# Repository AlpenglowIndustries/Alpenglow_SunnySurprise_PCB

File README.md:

# Alpenglow_SunnySurprise_PCB
Kicad files for learn to solder PCB

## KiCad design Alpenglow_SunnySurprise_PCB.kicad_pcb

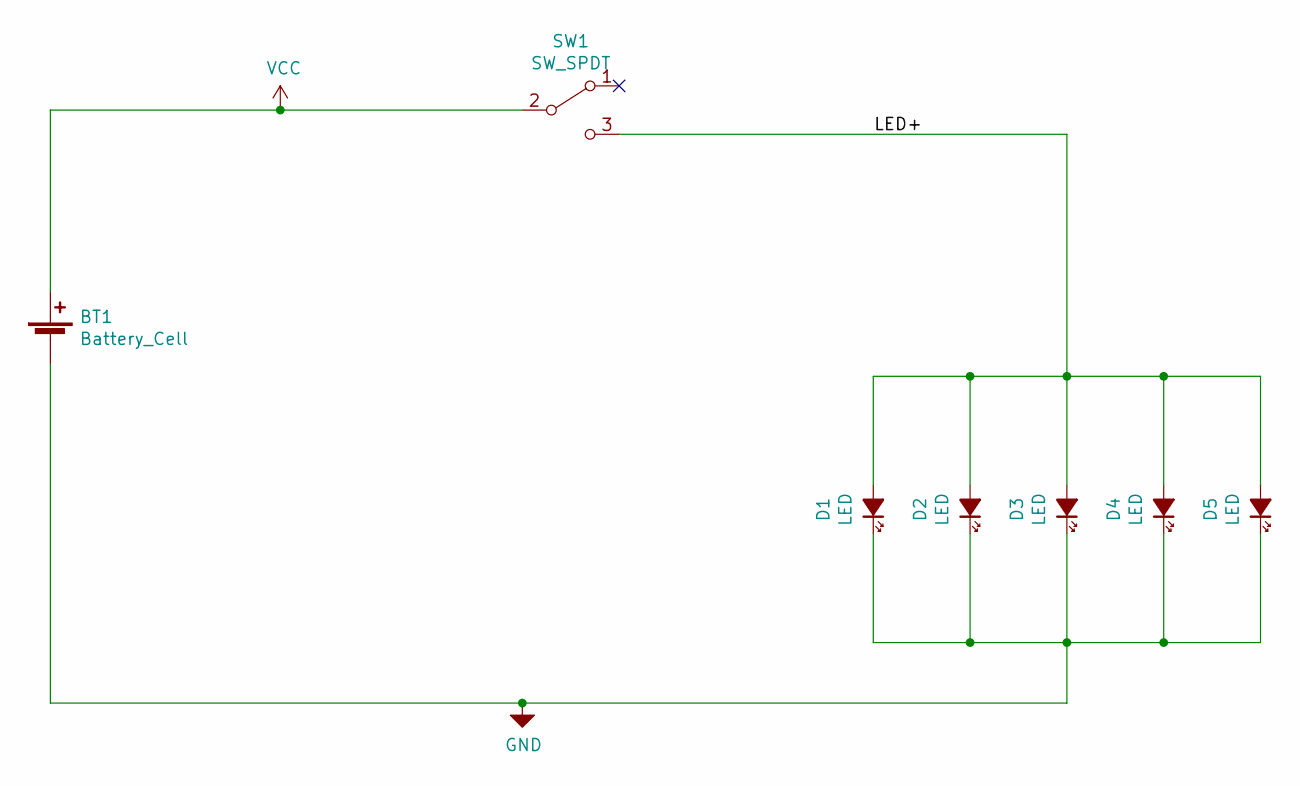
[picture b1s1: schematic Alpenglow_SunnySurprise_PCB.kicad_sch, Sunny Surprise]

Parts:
BT1: Battery_Cell; BatteryHolder_MPD_BK888_2032_THRU
D1, D2, D3, D4, D5: LED; LED_D5.0mm_Horizontal_Sun
SW1: SW_SPDT; Alpenglow_SW_SPDT_3pin_RTA

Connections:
/LED+: D1.2 (A), D2.2 (A), D3.2 (A), D4.2 (A), D5.2 (A), SW1.3 (C)
GND: BT1.2 (-), D1.1 (K), D2.1 (K), D3.1 (K), D4.1 (K), D5.1 (K)
VCC: BT1.1 (+), SW1.2 (B)

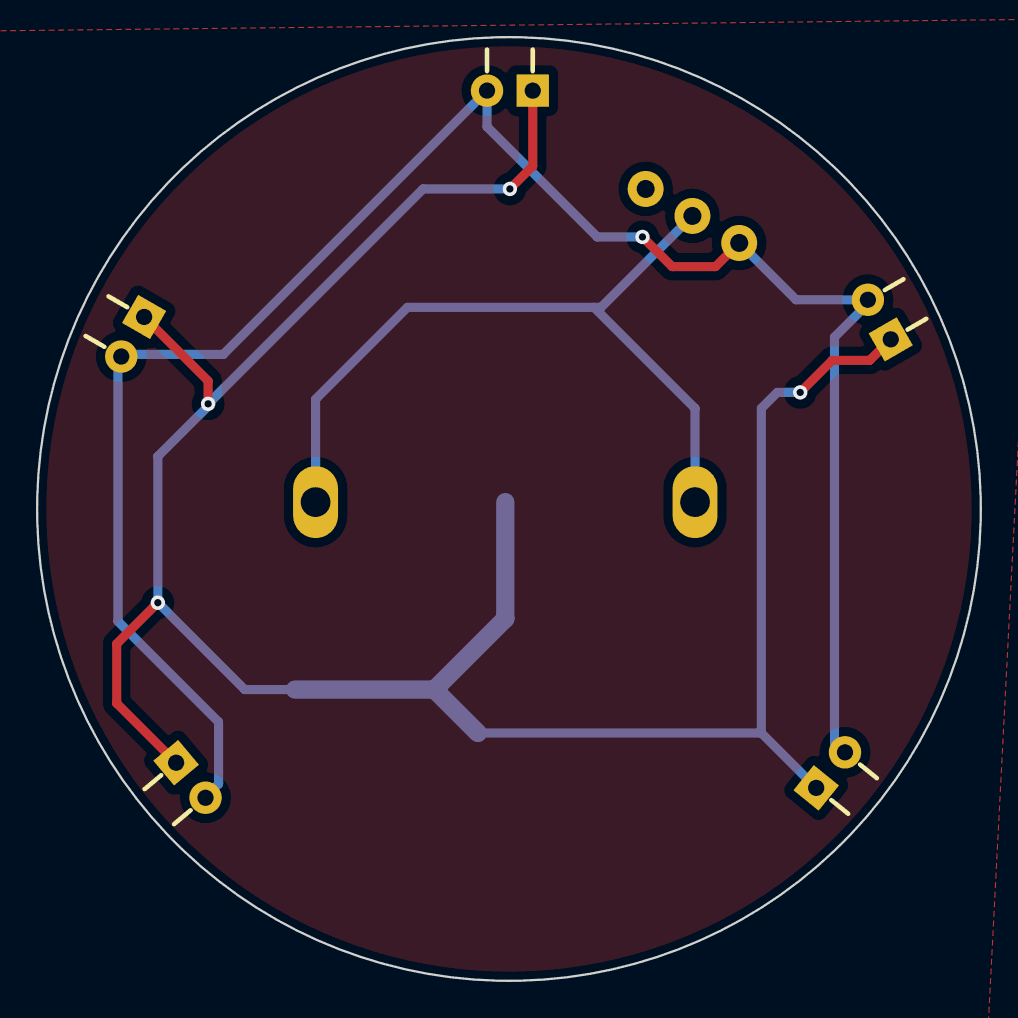
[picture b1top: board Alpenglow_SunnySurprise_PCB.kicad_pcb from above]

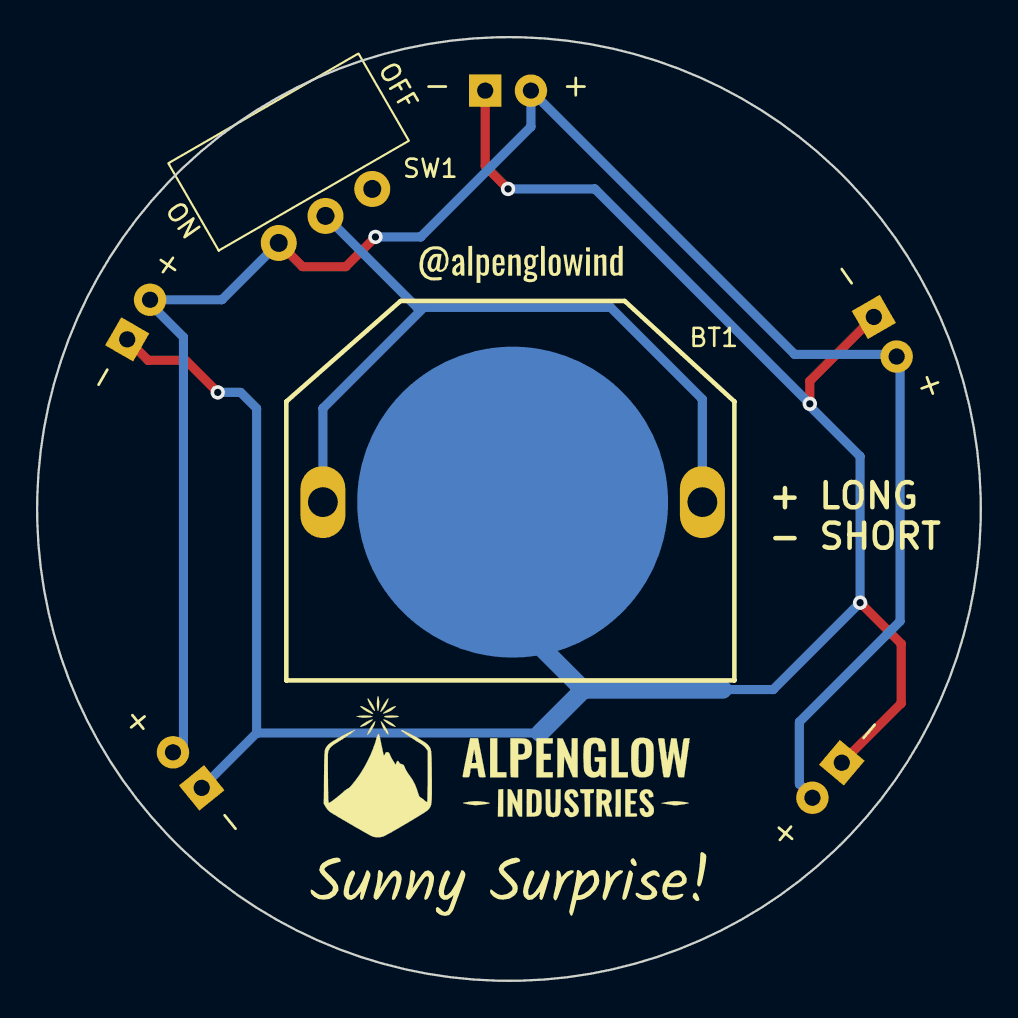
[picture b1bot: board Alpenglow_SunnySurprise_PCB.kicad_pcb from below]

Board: 2 copper layers, 52.4 x 52.4 mm, 7 parts (2 on the bottom side), 3 nets.

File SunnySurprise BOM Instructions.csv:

Line,RefDes,Type,Qty Kit,Qty PCB,Description,Manufacturer,Manufacturer Part No,,,,,,,,,,,,,,,,
1,"BT1, ",CONN,1,1,"Through hole, CR2032 battery holder",PengPeng Components Store,,,,,,,,,,,,,,,,,
2,"D1, D2, D3, D4, D5, ",LED,6,5,"LED, 5mm, Yellow, Colored lens, through hole",KY WIN ROBOT,,,,,,,,,,,,,,,,,
3,"SW1, ",SW_SPDT,1,1,"Right angle slide switch, SPDT, through hole",xin cheng electronic,SK12D07VG3,,,,,,,,,,,,,,,,
4,,PCB,1,,Sunny Surprise PCB,,,,,,,,,,,,,,,,,,
5,,,1,0,Adhesive-backed pin,,,,,,,,,,,,,,,,,,
6,,,1,0,Magnet,YuLe,,,,,,,,,,,,,,,,,
7,,,1,0,"CR2032, coin cell battery",pkcell,AG4,,,,,,,,,,,,,,,,
,,,,,,,,,,,,,,,,,,,,,,,
,,,,,,,,,,,,,,,,,,,,,,,
,,,,,,,,,,,,,,,,,,,,,,,
,,,,,,,,,,,,,,,,,,,,,,,
,,,,,,,,,,,,,,,,,,,,,,,
,,,,,,,,,,,,,,,,,,,,,,,
,,,,,,,,,,,,,,,,,,,,,,,
,,,,,,,,,,,,,,,,,,,,,,,
,,,,,,,,,,,,,,,,,,,,,,,
,,,,,,,,,,,,,,,,,,,,,,,
,,,,,,,,,,,,,,,,,,,,,,,
,,,,,,,,,,,,,,,,,,,,,,,
,,,,,,,,,,,,,,,,,,,,,,,
,,,,,,,,,,,,,,,,,,,,,,,
,,,,,,,,,,,,,,,,,,,,,,,
,,,,,,,,,,,,,,,,,,,,,,,
,,,,,,,,,,,,,,,,,,,,,,,
,,,,,,,,,,,,,,,,,,,,,,,
,,,,,,,,,,,,,,,,,,,,,,,
,,,,,,,,,,,,,,,,,,,,,,,
,,,,,,,,,,,,,,,,,,,,,,,
,,,,,,,,,,,,,,,,,,,,,,,
,,,,,,,,,,,,,,,,,,,,,,,
,,,,,,,,,,,,,,,,,,,,,,,
,,,,,,,,,,,,,,,,,,,,,,,
,,,,,,,,,,,,,,,,,,,,,,,
,,,,,,,,,,,,,,,,,,,,,,,
,,,,,,,,,,,,,,,,,,,,,,,
,,,,,,,,,,,,,,,,,,,,,,,
,,,,,,,,,,,,,,,,,,,,,,,
,,,,,,,,,,,,,,,,,,,,,,,
,,,,,,,,,,,,,,,,,,,,,,,
,,,,,,,,,,,,,,,,,,,,,,,
,,,,,,,,,,,,,,,,,,,,,,,
,,,,,,,,,,,,,,,,,,,,,,,
,,,,,,,,,,,,,,,,,,,,,,,
,,,,,,,,,,,,,,,,,,,,,,,
,,,,,,,,,,,,,,,,,,,,,,,
,,,,,,,,,,,,,,,,,,,,,,,
,,,,,,,,,,,,,,,,,,,,,,,
,,,,,,,,,,,,,,,,,,,,,,,
,,,,,,,,,,,,,,,,,,,,,,,
,,,,,,,,,,,,,,,,,,,,,,,
,,,,,,,,,,,,,,,,,,,,,,,
,,,,,,,,,,,,,,,,,,,,,,,
,,,,,,,,,,,,,,,,,,,,,,,
,,,,,,,,,,,,,,,,,,,,,,,
,,,,,,,,,,,,,,,,,,,,,,,
,,,,,,,,,,,,,,,,,,,,,,,
,,,,,,,,,,,,,,,,,,,,,,,
,,,,,,,,,,,,,,,,,,,,,,,
,,,,,,,,,,,,,,,,,,,,,,,
,,,,,,,,,,,,,,,,,,,,,,,
,,,,,,,,,,,,,,,,,,,,,,,
,,,,,,,,,,,,,,,,,,,,,,,
,,,,,,,,,,,,,,,,,,,,,,,
,,,,,,,,,,,,,,,,,,,,,,,
,,,,,,,,,,,,,,,,,,,,,,,
,,,,,,,,,,,,,,,,,,,,,,,
,,,,,,,,,,,,,,,,,,,,,,,
,,,,,,,,,,,,,,,,,,,,,,,
,,,,,,,,,,,,,,,,,,,,,,,
,,,,,,,,,,,,,,,,,,,,,,,
,,,,,,,,,,,,,,,,,,,,,,,
,,,,,,,,,,,,,,,,,,,,,,,
,,,,,,,,,,,,,,,,,,,,,,,
,,,,,,,,,,,,,,,,,,,,,,,
,,,,,,,,,,,,,,,,,,,,,,,
,,,,,,,,,,,,,,,,,,,,,,,
,,,,,,,,,,,,,,,,,,,,,,,
,,,,,,,,,,,,,,,,,,,,,,,

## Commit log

2022-04-01 Initial commit of all Kicad files
2022-05-04 Updated board design with new sun. Ordered prototypes
2022-05-20 Changed silkscreen so it's a circle instead of a square
2022-06-01 Updated Final Design
2022-06-03 final commit for ordering boards
2022-06-06 Changed Sun to be exposed copper. Added via so trace isn't going over exposed copper.
2022-06-07 Cleaned up unused layouts, generated gerbers, added sch template
2022-09-15 Updated board name font, updated @alpenglowind with oswald font
2022-09-16 Updated switch footprint
2022-10-27 updated BOM, Schematic PDF
2022-10-27 Added gitignore, changed BOM to CSV file
2024-01-03 Updated Switch, Removed GND pour and added GND traces, Updated artwork
2024-01-12 cleaned up some traces and text
2024-01-16 Updated font, Removed extra vias for GND traces, Renamed pwr net to LED+
2024-01-20 cleaned up short tracks, added fab notes, generated gerbers
